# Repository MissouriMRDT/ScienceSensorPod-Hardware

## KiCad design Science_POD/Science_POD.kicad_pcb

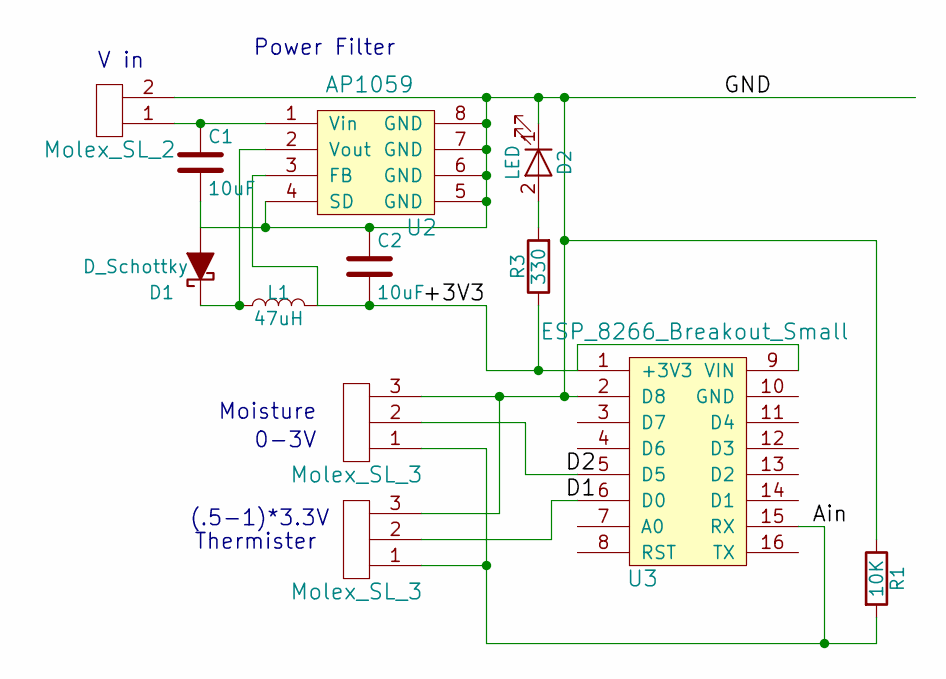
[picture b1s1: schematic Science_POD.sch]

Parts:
C1, C2: 10uF; C_0603_HandSoldering
D1: D_Schottky; C_0603_HandSoldering
D2: LED; D_1206
L1: 47uH; L_0603_HandSoldering
R1: 10K; R_0603_HandSoldering
R3: 330; R_0603_HandSoldering
U1: Molex_SL_2; MOLEX_SL_2
U2: AP1059; HTSOP-8-1EP_3.9x4.9mm_Pitch1.27mm
U3: ESP_8266_Breakout_Small
U4, U5: Molex_SL_3; MOLEX_SL_3

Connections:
/+3V3: C2.2, L1.2, R3.1, U2.3 (FB), U3.1 (+3V3), U3.9 (VIN)
/Ain: R1.2, U3.15 (RX), U4.1, U5.1; also elsewhere on the board
/D1: U3.6 (D0), U5.2; also elsewhere on the board
/D2: U3.5 (D5), U4.2
/GND: C1.2, C2.1, D1.2 (A), D2.1 (K), R1.1, U1.2, U2.4 (SD), U2.5 (GND), U2.6 (GND), U2.7 (GND), U2.8 (GND), U3.2 (D8), U4.3, U5.3
unnamed: C1.1, U1.1, U2.1 (Vin)
unnamed: D1.1 (K), L1.1, U2.2 (Vout)
unnamed: D2.2 (A), R3.2

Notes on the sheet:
V in
Power Filter
Thermister
Moisture
(.5-1)*3.3V
0-3V

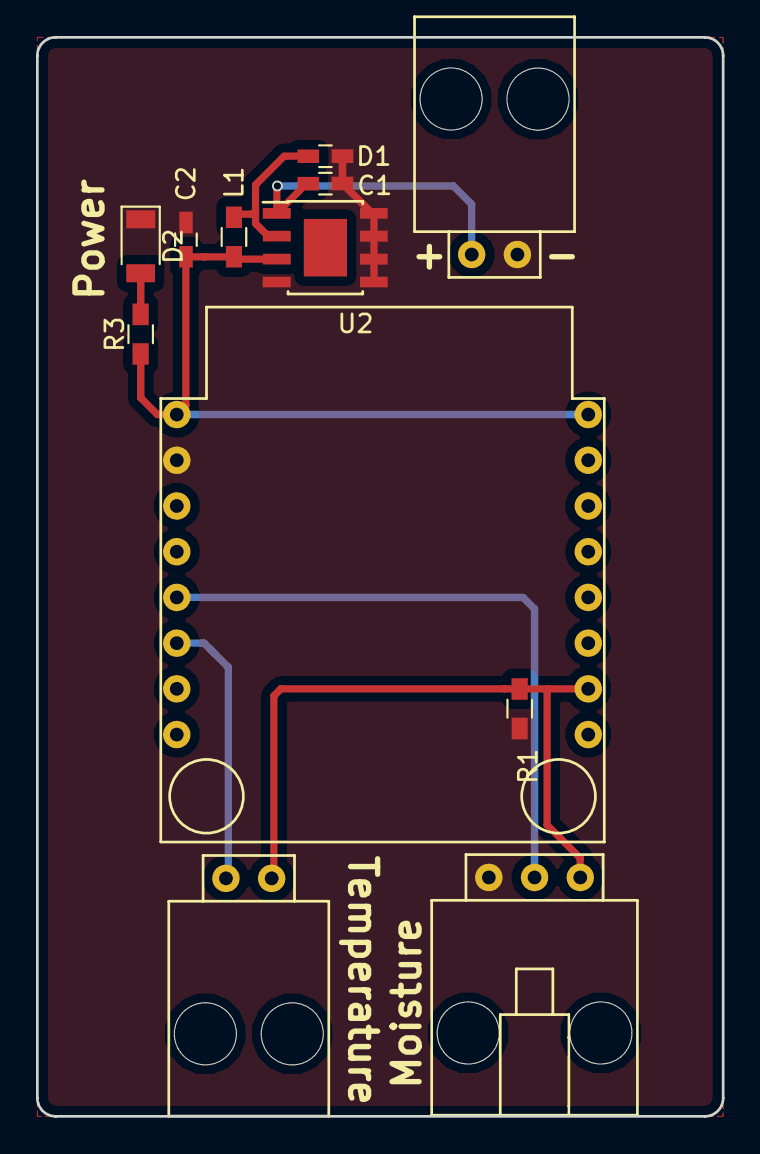
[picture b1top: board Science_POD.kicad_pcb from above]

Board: 2 copper layers, 38.1 x 59.9 mm, 12 parts (0 on the bottom side), 8 nets.

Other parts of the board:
Conn1: Molex_SL_2; MOLEX_SL_2_Horizontal

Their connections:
/Ain: Conn1.1; also elsewhere on the board
/D1: Conn1.2; also elsewhere on the board

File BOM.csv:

Id,Designator,Package,Quantity,Designation,Supplier and ref
1,"C1,C2",C_0603_HandSoldering,2,10uF,
2,L1,L_0603_HandSoldering,1,47uH,
3,R1,R_0603_HandSoldering,1,10K,
4,U1,MOLEX_SL_2,1,Molex_SL_2,
5,U2,HTSOP-8-1EP_3.9x4.9mm_Pitch1.27mm,1,AP1059,
6,U4,MOLEX_SL_3,1,Molex_SL_3,
7,D1,C_0603_HandSoldering,1,D_Schottky,
8,U3,ESP_8266_Breakout_Small,1,ESP_8266_Breakout_Small,
11,D2,D_1206,1,LED,
12,R3,R_0603_HandSoldering,1,330,
13,U5,MOLEX_SL_3_Horizontal,1,Molex_SL_3,

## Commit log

2018-03-23 cREATED SCHEMATIC AND BOARD
2018-03-26 finalised board
2018-03-28 Generated Final Gerbs
2018-04-24 Rev 2-added SL-3 for thermister. Fixed esp footprint
2018-04-29 Generated Gerbs
2018-05-03 Added BOM.csv
2018-05-03 Added BOM CSV
2018-05-04 Chenged thermister back to SL-2
2018-05-29 Buck Converter had incorrect value
    Corrected to AP1509.
2018-08-14 Added gitatributes
2018-08-14 Test change to javascript
2018-08-14 Test gitattributes
2018-08-14 Removed gitattributes
